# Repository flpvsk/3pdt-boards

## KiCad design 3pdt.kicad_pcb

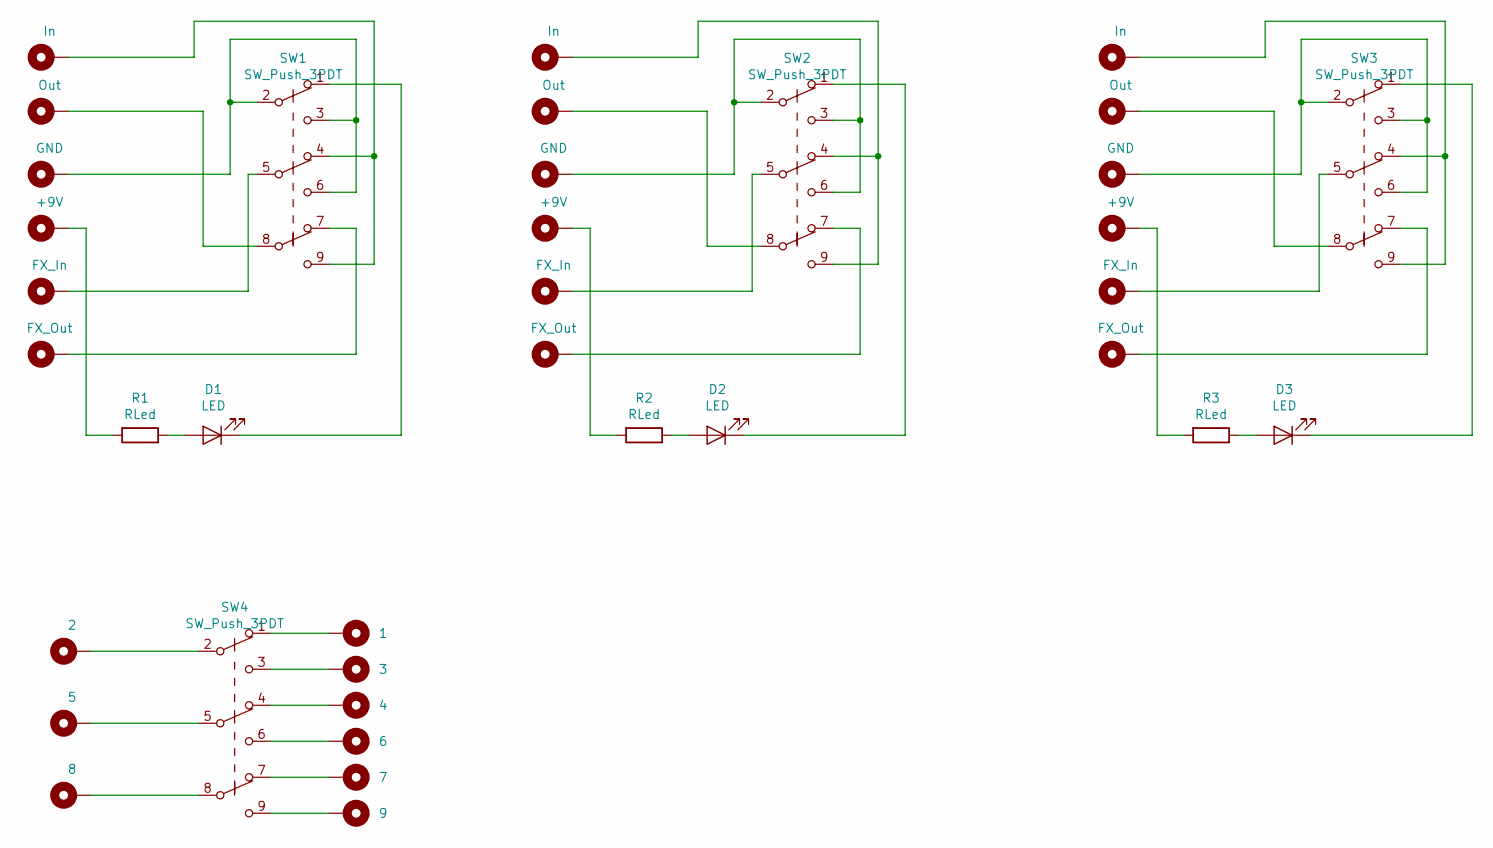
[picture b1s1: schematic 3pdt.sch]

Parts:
D1, D2, D3: LED; 3MM_1
H1: In; PinHeader_1x01_P2.54mm_Vertical
H2: Out; PinHeader_1x01_P2.54mm_Vertical
H3: GND; PinHeader_1x01_P2.54mm_Vertical
H4: +9V; PinHeader_1x01_P2.54mm_Vertical
H5: FX_In; PinHeader_1x01_P2.54mm_Vertical
H6: FX_Out; PinHeader_1x01_P2.54mm_Vertical
H7, H13: In; SolderWirePad_1x01_Drill1.5mm
H8, H14: Out; SolderWirePad_1x01_Drill1.5mm
H9, H15: GND; SolderWirePad_1x01_Drill1.5mm
H10, H16: +9V; SolderWirePad_1x01_Drill1.5mm
H11, H17: FX_In; SolderWirePad_1x01_Drill1.5mm
H12, H18: FX_Out; SolderWirePad_1x01_Drill1.5mm
H19: 2; PinHeader_1x01_P2.54mm_Vertical
H20: 5; PinHeader_1x01_P2.54mm_Vertical
H21: 8; PinHeader_1x01_P2.54mm_Vertical
H22: 1; PinHeader_1x01_P2.54mm_Vertical
H23: 3; PinHeader_1x01_P2.54mm_Vertical
H24: 4; PinHeader_1x01_P2.54mm_Vertical
H25: 6; PinHeader_1x01_P2.54mm_Vertical
H26: 7; PinHeader_1x01_P2.54mm_Vertical
H27: 9; PinHeader_1x01_P2.54mm_Vertical
R1, R2, R3: RLed; 0.3_22.B
SW1, SW2, SW3, SW4: SW_Push_3PDT; 3PDT.LUGS.FLPVSK

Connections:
unnamed: D1.1 (K), SW1.1 (A)
unnamed: D1.2 (A), R1.1
unnamed: D2.1 (K), SW2.1 (A)
unnamed: D2.2 (A), R2.1
unnamed: D3.1 (K), SW3.1 (A)
unnamed: D3.2 (A), R3.1
unnamed: H1.1, SW1.4 (A), SW1.9 (C)
unnamed: H2.1, SW1.8 (B)
unnamed: H3.1, SW1.2 (B), SW1.3 (C), SW1.6 (C)
unnamed: H4.1, R1.2
unnamed: H5.1, SW1.5 (B)
unnamed: H6.1, SW1.7 (A)
unnamed: H7.1, SW2.4 (A), SW2.9 (C)
unnamed: H8.1, SW2.8 (B)
unnamed: H9.1, SW2.2 (B), SW2.3 (C), SW2.6 (C)
unnamed: H10.1, R2.2
unnamed: H11.1, SW2.5 (B)
unnamed: H12.1, SW2.7 (A)
unnamed: H13.1, SW3.4 (A), SW3.9 (C)
unnamed: H14.1, SW3.8 (B)
unnamed: H15.1, SW3.2 (B), SW3.3 (C), SW3.6 (C)
unnamed: H16.1, R3.2
unnamed: H17.1, SW3.5 (B)
unnamed: H18.1, SW3.7 (A)
unnamed: H19.1, SW4.2 (B)
unnamed: H20.1, SW4.5 (B)
unnamed: H21.1, SW4.8 (B)
unnamed: H22.1, SW4.1 (A)
unnamed: H23.1, SW4.3 (C)
unnamed: H24.1, SW4.4 (A)
unnamed: H25.1, SW4.6 (C)
unnamed: H26.1, SW4.7 (A)
unnamed: H27.1, SW4.9 (C)

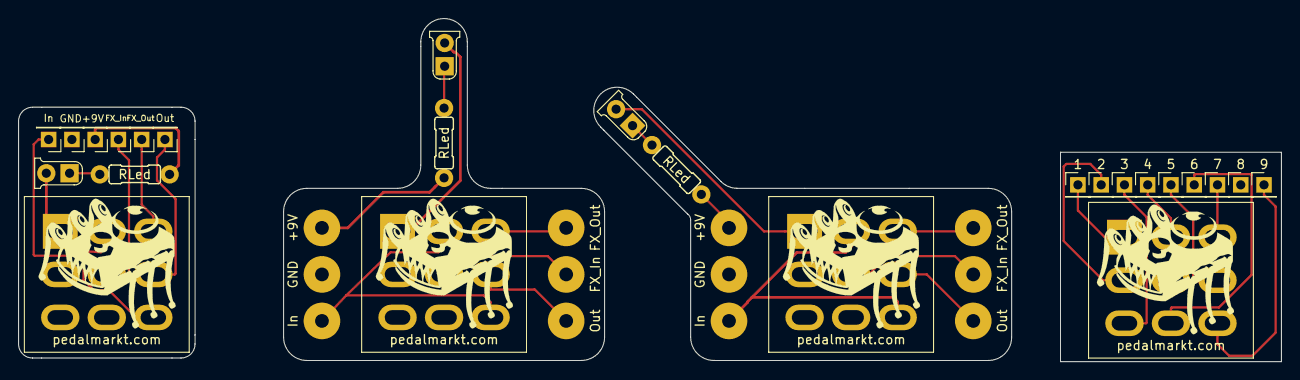
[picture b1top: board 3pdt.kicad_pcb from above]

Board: 2 copper layers, 137.9 x 37.5 mm, 37 parts (0 on the bottom side), 33 nets.

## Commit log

2020-11-21 Init
